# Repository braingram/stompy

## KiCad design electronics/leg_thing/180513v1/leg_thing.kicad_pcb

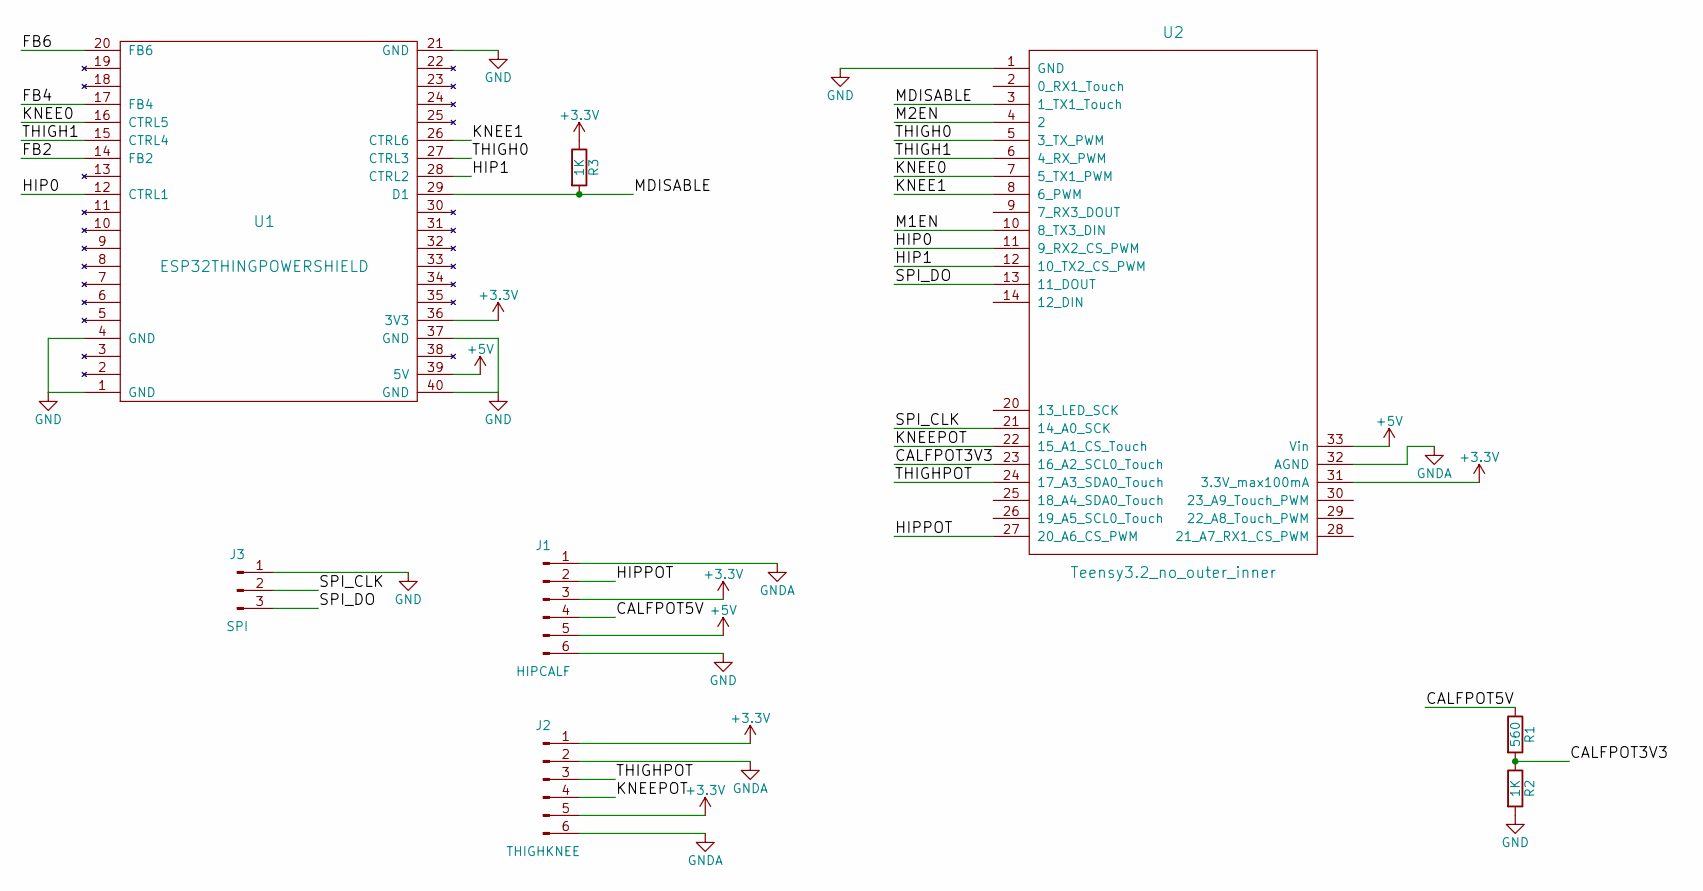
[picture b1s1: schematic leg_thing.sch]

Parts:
J1: HIPCALF; MOLEX6PIN
J2: THIGHKNEE; MOLEX6PIN
J3: SPI; Pin_Header_Straight_1x03_Pitch2.54mm
R1: 560; R_Axial_DIN0207_L6.3mm_D2.5mm_P10.16mm_Horizontal
R2: 1K; R_Axial_DIN0207_L6.3mm_D2.5mm_P10.16mm_Horizontal
R3: 1K; R_1206_HandSoldering
U1: ESP32THINGPOWERSHIELD
U2: Teensy3.2_no_outer_inner; Teensy30_31_32_LC_NO_INNER_OUTER

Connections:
+3V3: J1.3, J2.1, J2.5, R3.1, U1.36 (3V3), U2.31 (3.3V_max100mA)
+5V: J1.5, U1.39 (5V), U2.33 (Vin)
/CALFPOT3V3: R1.2, R2.1, U2.23 (16_A2_SCL0_Touch)
/CALFPOT5V: J1.4, R1.1
/FB2: U1.14 (FB2)
/FB4: U1.17 (FB4)
/FB6: U1.20 (FB6)
/HIP0: U1.12 (CTRL1), U2.11 (9_RX2_CS_PWM)
/HIP1: U1.28 (CTRL2), U2.12 (10_TX2_CS_PWM)
/HIPPOT: J1.2, U2.27 (20_A6_CS_PWM)
/KNEE0: U1.16 (CTRL5), U2.7 (5_TX1_PWM)
/KNEE1: U1.26 (CTRL6), U2.8 (6_PWM)
/KNEEPOT: J2.4, U2.22 (15_A1_CS_Touch)
/M1EN: U2.10 (8_TX3_DIN)
/M2EN: U2.4 (2)
/MDISABLE: R3.2, U1.29 (D1), U2.3 (1_TX1_Touch)
/SPI_CLK: J3.2, U2.21 (14_A0_SCK)
/SPI_DO: J3.3, U2.13 (11_DOUT)
/THIGH0: U1.27 (CTRL3), U2.5 (3_TX_PWM)
/THIGH1: U1.15 (CTRL4), U2.6 (4_RX_PWM)
/THIGHPOT: J2.3, U2.24 (17_A3_SDA0_Touch)
GND: J1.6, J3.1, R2.2, U1.1 (GND), U1.4 (GND), U1.21 (GND), U1.37 (GND), U1.40 (GND), U2.1 (GND)
GNDA: J1.1, J2.2, J2.6, U2.32 (AGND)

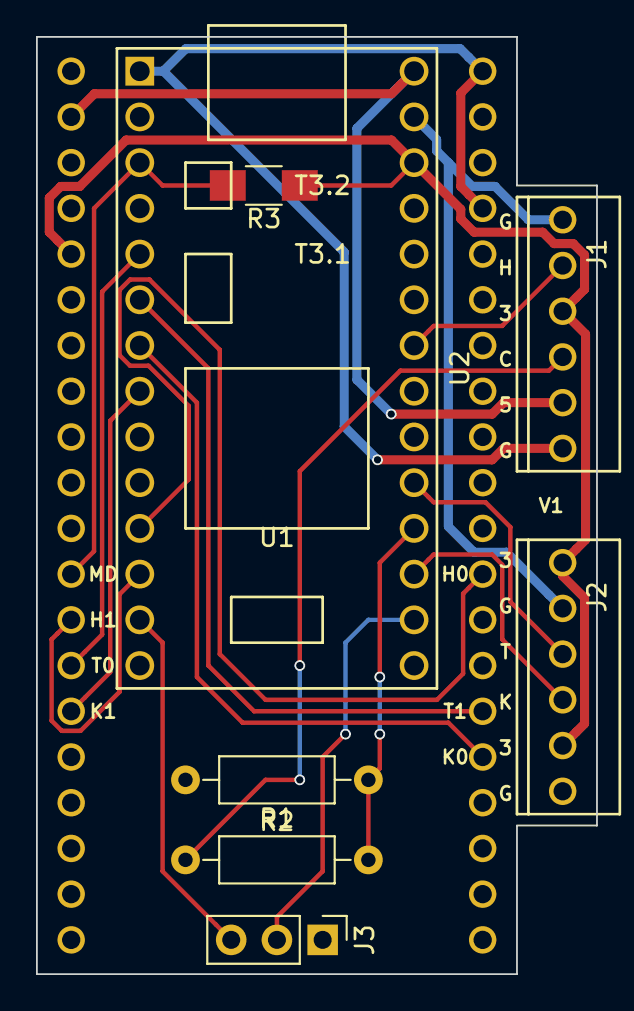
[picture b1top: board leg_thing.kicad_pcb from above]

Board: 2 copper layers, 31.1 x 52.1 mm, 8 parts (0 on the bottom side), 18 nets.

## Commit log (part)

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2016-07-17 adding ros submodule
2016-07-17 making non-class trajectory functions
2016-07-23 adding body rotations
2016-07-24 removing _matrix from transform names, updated body rotations, added follow transform
2016-07-24 readding body moves and leg lifts to stand_trajectory test
2016-08-14 adding fake joystick publisher
2016-08-14 trying out different approach to gait point generation
2016-08-18 working on motion control planning
2016-08-20 renaming joints
2016-08-20 adding some test code for a ros leg
2016-08-21 started leg code
2016-08-21 adding heartbeat code
2016-08-21 testing estop messages
2016-08-23 updating leg firmware
2016-08-27 adding time sync example so leg node can keep track of teensy time
2016-08-27 updating action_server example, adding action_client example
2016-08-28 adding clock offset measurement to leg node
2016-08-28 testing leg node time sync
2016-09-03 docs test
2016-09-05 some gait work
2016-09-05 state machine test, adding position leg to load
2016-09-06 adding body rotations to state machine test
2016-09-07 filling out state machine, adding per-joint control, making less jerky, adding position legs and stand
2016-09-11 adding rotate_about_point, updateing state_machine2
2016-09-11 changing set_stop to soft stop
2016-09-11 removing old _current_point caching
2016-09-17 working on trajectory passing
2016-09-17 firmware: bug with advance_move_index
2016-09-20 rewrite of joint sensor conversion, writing bag publisher that restamps times
2016-09-21 docs
2016-10-16 adding stompy test sketch
2016-10-27 adding simple leg script
2016-10-30 direct drive firmware, enabling motors
2016-11-09 updating direct drive firmware for current feedback
2016-11-13 updating direct drive firmware for system voltage monitoring
2016-11-21 updated restriction demo
2016-11-22 start of restriction control in state machine
2017-01-25 Adding cylinder specs
2017-02-04 adding oil to hydraulics doc
2017-10-14 updating restriction test to use tk
2017-10-15 adding calf trig notes/test
2017-10-22 finishing out calf trig and comparing against linear model
2018-02-03 cleaning up tests and docs
2018-02-03 adding leg/body drawings
2018-02-03 add carb info
2018-02-03 tested teensy class
2018-02-04 setup ps3 controller, start on restriction
2018-02-08 simple single leg controller with joystick
2018-02-08 single_leg: added restriction control
2018-02-08 change r_thresh for now
2018-02-10 adding logging, change joystick update, improved restriction control
2018-02-10 adding load_dir function to log module
2018-02-10 increase p and i for fr leg, now actually logging pid error
2018-02-11 slight rearrange of res calc, adding dr smoothing
2018-02-11 allow for change in speed during restriction sending
2018-02-11 a bit of tuning for the fake led pids
2018-02-18 ui in qt
2018-02-18 work on leg ui
2018-02-23 3d leg display test
2018-02-23 slightly decrease default foot coord velocity
2018-02-25 gl widget context menu
2018-02-26 integrating single leg controller with qt ui
2018-03-04 ui updates
2018-03-13 working on multileg
2018-03-14 fake teensies working for testing multileg controller
2018-03-15 fake legs starting to take shape
2018-03-17 restructuring restriction control
2018-03-17 res control reorg done, halting unhalting works
2018-03-18 joystick working with multileg controller, mode switching working
2018-03-20 updating limit calculations
2018-03-20 add modes menu
2018-03-21 rotated body coordinates so y+ is forward
2018-04-11 when connecting to 1 leg, don't compute neighbors
2018-04-11 splitting logs per leg
2018-04-12 wip testing estop on limit
2018-04-18 arc mode working
2018-04-18 adding start of calibration routine framework
2018-04-22 updating log file reading for multi-leg logs, added function to get adc min/max
2018-04-22 working on speed control, needs ui and testing
2018-04-22 more leg calibrations
2018-04-28 initial map of body rotations to joystick
2018-04-28 swap xy for body move rotations
2018-04-29 throttling joystick input
2018-05-06 reverting joystick throttle, didn't work on robot
2018-05-12 add function to compute calf angle relative to ground
2018-05-13 adding function to generate calf calibrations
2018-05-13 leg 2 calibration
2018-05-17 minor bug when switching to restriction mode
2018-05-20 reducing angular speed, setting max feet up to 1
2018-05-22 fixed esp32thingpowershield footprint, started new layout
2018-05-23 electronics: switching to 6 pin molex connectors
2018-05-24 electronics: updating sch and pcb pdfs
2018-05-26 testing different pid seed times
2018-05-27 ui: adding speeds, etc
2018-05-27 ui: attached seed time ui widgets
2018-05-27 add option to noramlize log times when plotting
2018-05-28 res: changing lower to allow for more slop
2018-05-30 res: bringing out height slop as a parameter
2018-06-02 adding manual restriction modifier
2018-06-03 working on sorting out joystick to arc mapping
2018-06-05 reducing some speeds
2018-06-05 adding crab walk and rise/lower to joystick vectoring
2018-06-12 matrix mode and restriction curves
2018-06-13 fixed velocity plan sending
2018-06-16 working matrix mode
2018-06-19 pulling leg res params into main cfg
2018-06-20 changing estop propagation to avoid infinite loops
2018-06-23 better foot swing positionsg
2018-06-23 updating ui to include swing parameters
2018-06-24 cleaning up res config, adding height label
2018-06-24 adjusting restriction cfg
2018-06-30 fixing x with vertical calf, adding x at calf angle
2018-07-03 updating leg thing pdfs
2018-07-08 testing body code, report logging working
2018-07-08 adding body reports to ui
2018-07-12 minor format change for rpm sensor
2018-07-17 use lower instead of lift height to plan swing targets
2018-08-05 getting dither working
2018-09-09 fixing res halt, adding loop stats reporting
2018-09-14 making the 4 ms plan tick time into a variable
2018-10-04 split future and seed times, make seed time constant
2018-10-04 start of calibration/diagnostic script
2018-10-05 adding print_joystick.py test
2018-10-15 adding initial test script for non-opengl 3d view
2018-10-15 starting dynamic remap of ps3 code-to-button map
2018-10-15 remapping ps3 joystick buttons to not need pressure sensing on shoulder buttons
2018-10-15 adding relative axes to print_joystick
2018-10-17 all but support triangle and plot back in place
2018-10-18 pid plot nogl working, switch leg and body displays to right hand coords
2018-10-21 limit nogl paints to 10 hz
2018-10-21 reset restriction halt state on enable
2018-10-27 making stompy.__main__
2018-10-27 cleanup ui directory
2018-10-27 making body move rotations match for sim and real bot
2018-10-27 ui bug: res.cfg.speeds.angular not editable
2018-10-28 setting dither for all joints
2018-11-12 updating some speeds
2018-11-12 log find adc limits now returns values
2018-11-18 fix limit calc to use limited hip length for non-middle legs
2018-11-18 working on restriction omni/crab walking, about to try all moves as rotationsg
2018-11-18 refactor restriction target\n now turns and omni walking both work as rotations about a point
2018-12-02 fixing omni x axis
2018-12-28 updates to match firmware updates
2018-12-29 adjusting pid values
2018-12-30 decrease log file size
2018-12-30 set plan_step from first connected leg
2019-01-10 fix missing PLAN_TICK for fake teensies
2019-01-12 add debug print
2019-01-13 leg 4 calf recal after sensor wiring work
2019-01-13 adding profiling tests
2019-01-15 fix ui leg selection, change io polling time, change fake leg pid
2019-01-17 add selected leg highlighting
2019-02-09 adding sensor noise to fake leg
2019-02-09 add log to res control, fix res unhalt
2019-02-17 add calibration menu, save/load cal in home directory, online calf zero point setting
2019-02-17 fixed saved calf cal format
2019-02-17 correct calf calibration mgr calls
2019-02-22 WIP: steel joystick python code
2019-02-23 ui: estop, height, support triangle
2019-02-23 adding calf angle to restriction, normalizing res values
2019-02-23 adding buttons to steel joystick
2019-02-23 test script to plot leg res
2019-02-23 fixed bug where height calc caused connection errors
2019-02-25 added settings: prevent_leg_xy_when_loaded, set_height_on_mode_select
2019-02-25 adding sit_stand mode with pure z move
2019-03-14 adding test for multi-touch input, seems to require pyqt5
2019-03-17 attempt to make ui work with both qt4 and 5
2019-03-17 qt4/5 work
2019-03-22 wip remote interface, just want to save code state before gutting client
2019-03-22 remote client and server working
    communicate using something like rpc but more pythonic
    over websockets. Support the following:
    get/set/getitem/setitem/call/signal
2019-03-22 starting to work on remote ui
2019-03-23 remote ui working
2019-03-23 adding remote_ui to __main__
2019-04-07 starting to unify remote and local ui
2019-04-09 switching to remote ui as default
2019-04-10 getting pid config working again in remote display
2019-04-11 removing unused restriction cfg
2019-04-11 rename ui.remote to ui.ui
2019-04-12 ui: add swipes
2019-04-13 adding change in height to restriction control
2019-04-17 odometer/pose history working, needs optimization
2019-04-23 making stompy python3 compatible
2019-04-27 adding fake terrain
2019-04-27 moving joystick to remote side, starting ui for fake joystick
2019-04-28 adding missing return statement when terrain.png is gone
2019-05-05 adding start of playback (dance) code
2019-05-27 restriction calf angle settings in degrees, setting target to 10 degrees
2019-05-30 lots of remote ui work
2019-06-03 updating parameters from recent walking
2019-06-08 wip backend support triangle calc, log py3 fixes, starting unification of kinematics
2019-06-09 cleanup
2019-06-15 bringing mode and leg select out to ui radio buttons
2019-06-16 adding speed slider
2019-06-16 fixing remote deadman
2019-06-19 updaing ui to use imu
2019-06-22 formatting docs
2019-06-22 Adding some more weights to doc
2019-06-22 Adding (rough) spine weight from CAD/gazebo
2019-06-22 removed print
2019-06-23 adding COG calc and display
2019-06-23 testing on bot
2019-07-06 faking imu readings for cog calcs, verified directions
2019-07-09 changing inputdialog to custom to make more touch friendly
2019-07-22 remove deadman timeout, allow unhalt during wait, res param changes
2019-07-24 removing pyqt4
2019-07-25 adding disable_joystick parameter, fixing remote stop
2019-07-25 removing more leftover deadman timeout code
2019-07-25 more cosmetic adjustments to ui
2019-07-28 fixing dialog for negative values, display restriction 'center' positions
2019-07-29 adding foot center offset code
2019-07-30 adding spot for and first stab at body calibration
2019-08-01 shiftable leg centers, use projected restriction, fixing halt/unhalt bug, adding halt and res states to ui
2019-08-01 update requirements.txt for only pyqt5, remove extra print
2019-08-06 calf load and imu (needs verification) working in sim
2019-09-14 changes to restriction calculation, tuning simulation
2019-09-14 compute ground slope using imu and leg positions
2019-09-28 adding mode for moving front legs together
2019-11-10 fix ui value bounds, disable front pair mode, changes to leg wiggle playback
2019-11-24 swap points for cross product to keep z positive
2019-11-24 adding parameter for height control
2019-12-17 add param for autoheight thresh, leg center shift thresholds
2020-01-05 restriction relative to center foot position
2020-01-26 adding more log output to should_lift
2020-01-26 fix should_lift y/z swap bug
2020-01-26 relaying halt signal from res body to legs, if res modifier is non 0 = should lift
2020-01-30 adding notes for reorg
2020-02-02 moving some code from restriction/leg to kinematics/leg
2020-02-02 switching functions from numpy to math
2020-02-02 reorg how halt/unhalt happens and how leg plans are sent
2020-02-02 enable odo when not halted
2020-02-04 increase leg speed if running in nosim sim
2020-02-16 adding write_leg_number script
2020-03-15 updating requirements
